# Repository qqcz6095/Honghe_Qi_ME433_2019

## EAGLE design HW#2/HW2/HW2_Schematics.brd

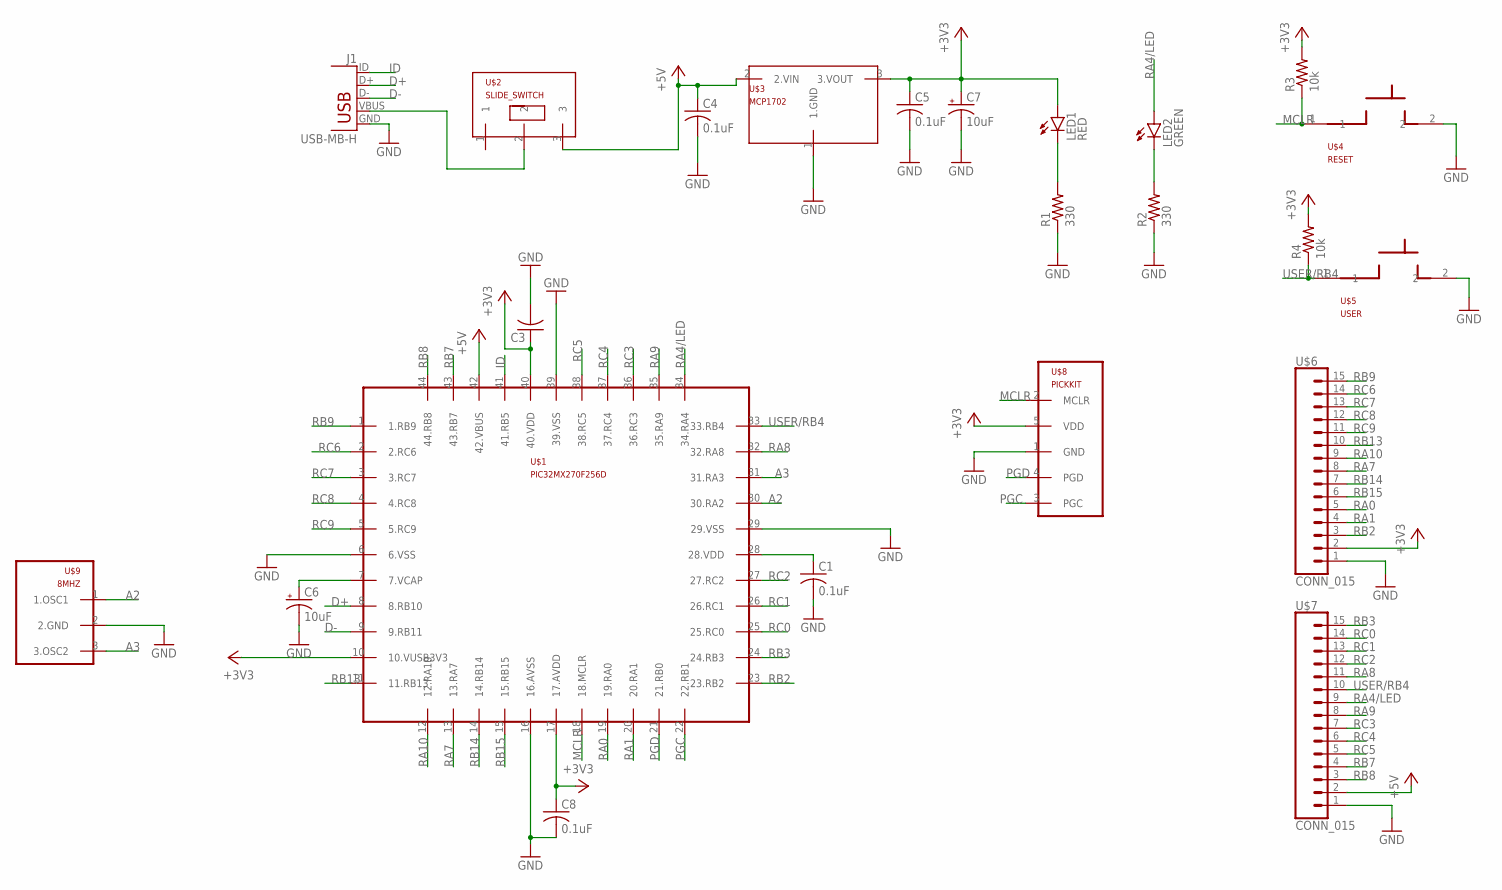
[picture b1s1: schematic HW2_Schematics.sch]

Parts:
C1, C4, C5, C8: 0.1uF; C025-025X050
C3: C-US025-025X050; C025-025X050
C6, C7: 10uF; B45181B
J1: USB-MB-H
LED1: RED; LED3MM
LED2: GREEN; LED3MM
R1, R2: 330; 0207/10
R3, R4: 10k; 0207/10
U$1: PIC32MX270F256D; TQFP44
U$2: SLIDE_SWITCH
U$3: MCP1702; TO92
U$4: RESET; PUSHBUTTON
U$5: USER; PUSHBUTTON
U$6, U$7: CONN_015; 1X15
U$8: PICKKIT; 1X05
U$9: 8MHZ; OSC

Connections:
+3V3: C3.1, C5.1, C7.+, C8.1, LED1.A, R3.2, R4.2, U$1.10 (10.VUSB3V3), U$1.17 (17.AVDD), U$1.40 (40.VDD), U$3.3 (3.VOUT), U$6.2, U$8.5 (VDD)
+5V: C4.1, U$1.42 (42.VBUS), U$2.3, U$3.2 (2.VIN), U$7.2
A2: U$1.30 (30.RA2), U$9.1 (1.OSC1)
A3: U$1.31 (31.RA3), U$9.3 (3.OSC2)
D+: J1.D+, U$1.8 (8.RB10)
D-: J1.D-, U$1.9 (9.RB11)
GND: C1.2, C3.2, C4.2, C5.2, C6.-, C7.-, C8.2, J1.GND, R1.1, R2.1, U$1.6 (6.VSS), U$1.16 (16.AVSS), U$1.29 (29.VSS), U$1.39 (39.VSS), U$3.1 (1.GND), U$4.2, U$5.2, U$6.1, U$7.1, U$8.1 (GND), U$9.2 (2.GND)
ID: J1.ID, U$1.41 (41.RB5)
MCLR: R3.1, U$1.18 (18.MCLR), U$4.1, U$8.2 (MCLR)
unnamed: J1.VBUS, U$2.2
unnamed: LED1.K (C), R1.2
unnamed: LED2.K (C), R2.2
unnamed: C6.+, U$1.7 (7.VCAP)
unnamed: C1.1, U$1.28 (28.VDD)
PGC: U$1.22 (22.RB1), U$8.3 (PGC)
PGD: U$1.21 (21.RB0), U$8.4 (PGD)
RA0: U$1.19 (19.RA0), U$6.5
RA1: U$1.20 (20.RA1), U$6.4
RA4/LED: LED2.A, U$1.34 (34.RA4), U$7.9
RA7: U$1.13 (13.RA7), U$6.8
RA8: U$1.32 (32.RA8), U$7.11
RA9: U$1.35 (35.RA9), U$7.8
RA10: U$1.12 (12.RA10), U$6.9
RB2: U$1.23 (23.RB2), U$6.3
RB3: U$1.24 (24.RB3), U$7.15
RB7: U$1.43 (43.RB7), U$7.4
RB8: U$1.44 (44.RB8), U$7.3
RB9: U$1.1 (1.RB9), U$6.15
RB13: U$1.11 (11.RB13), U$6.10
RB14: U$1.14 (14.RB14), U$6.7
RB15: U$1.15 (15.RB15), U$6.6
RC0: U$1.25 (25.RC0), U$7.14
RC1: U$1.26 (26.RC1), U$7.13
RC2: U$1.27 (27.RC2), U$7.12
RC3: U$1.36 (36.RC3), U$7.7
RC4: U$1.37 (37.RC4), U$7.6
RC5: U$1.38 (38.RC5), U$7.5
RC6: U$1.2 (2.RC6), U$6.14
RC7: U$1.3 (3.RC7), U$6.13
RC8: U$1.4 (4.RC8), U$6.12
RC9: U$1.5 (5.RC9), U$6.11
USER/RB4: R4.1, U$1.33 (33.RB4), U$5.1, U$7.10

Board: 2 copper layers, 23 parts (1 on the bottom side), 42 nets, no tracks yet.

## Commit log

2019-04-04 1st commit
2019-04-04 Test
2019-04-04 Setup
2019-04-04 TRIS and LAT
2019-04-04 Final
2019-04-04 Pictures and Video
2019-04-07 Copy Library
2019-04-08 Library Made
2019-04-08 Library Update
2019-04-08 Schematic
2019-04-09 Board File Created
2019-04-11 Board Created
2019-04-11 Board Finished
2019-04-11 Gerber File Created
2019-04-16 Code
2019-04-16 Pictures
2019-04-17 I2C light on
2019-04-17 I2C complete
2019-04-21 Rename Folder
2019-04-21 Code Created
2019-04-22 updated screen to 10hz
2019-04-23 demo video uploaded
2019-04-23 HW created
2019-04-24 who am i
2019-04-24 cross bar
2019-04-26 Move folder an upload ciruit diagram for HW#5
2019-04-29 harmony for hw7 updated
2019-05-03 HW_9 Created
2019-05-04 HW9 LCD UI Created
2019-05-05 HW9 Updated
2019-05-07 HW_10 Update
2019-05-07 HW9 eveything works
2019-05-07 HW9 code cleanup
2019-05-07 HW10 demo video
2019-05-09 HW10_Update
2019-05-10 HW9_ili9341_PIC32.h split into *.h and *.c
2019-05-11 HW12 Complete
2019-05-12 HW11 Setup
2019-05-13 HW11 MAF + IIR
2019-05-13 HW11 filters all working
2019-05-18 HW13 Picture Upload
2019-05-18 Picture rename
2019-05-21 HW13_Picture Uploaded
2019-05-21 HW14 Created
2019-06-04 HW15 created and plot done kinda
2019-06-04 HW15 update
2019-06-09 Car Body Updated
2019-06-10 HW15 works
2019-06-13 HW16 update
2019-06-14 Pictures updated
